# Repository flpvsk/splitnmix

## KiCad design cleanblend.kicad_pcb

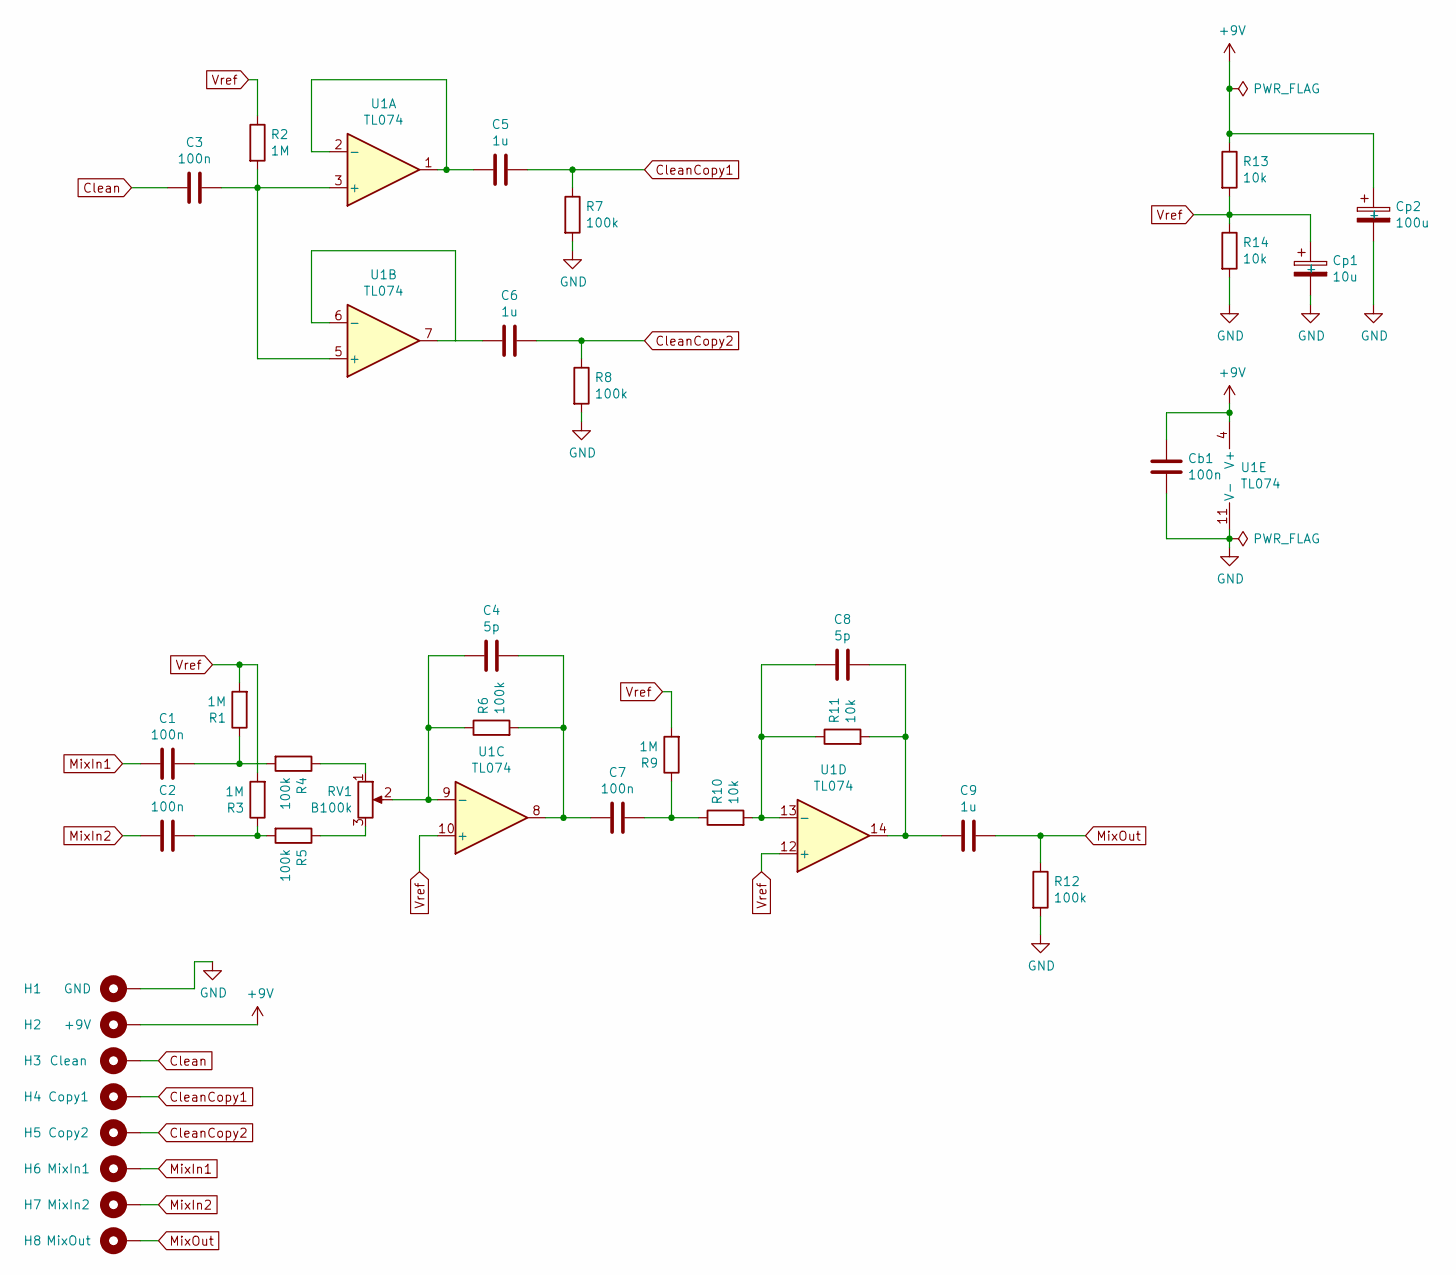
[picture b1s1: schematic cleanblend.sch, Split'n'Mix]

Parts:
C1, C2, C3, C7: 100n; C_0805_2012Metric_Pad1.15x1.40mm_HandSolder; JLC C49678
C4, C8: 5p; C_0603_1608Metric_Pad1.05x0.95mm_HandSolder; JLC C93045
C5, C6, C9: 1u; C_0805_2012Metric_Pad1.15x1.40mm_HandSolder; JLC C28323
Cb1: 100n; C_0805_2012Metric_Pad1.15x1.40mm_HandSolder; JLC C49678
Cp1: 10u; CP_Elec_5x5.3; JLC C249452
Cp2: 100u; CP_Elec_6.3x7.7; JLC C171732
H1: GND; PinHeader_1x01_P2.54mm_Long_Front_Back
H2: +9V; PinHeader_1x01_P2.54mm_Long_Front_Back
H3: Clean; PinHeader_1x01_P2.54mm_Long_Front_Back
H4: Copy1; PinHeader_1x01_P2.54mm_Long_Front_Back
H5: Copy2; PinHeader_1x01_P2.54mm_Long_Front_Back
H6: MixIn1; PinHeader_1x01_P2.54mm_Long_Front_Back
H7: MixIn2; PinHeader_1x01_P2.54mm_Long_Front_Back
H8: MixOut; PinHeader_1x01_P2.54mm_Long_Front_Back
R1, R2, R3, R9: 1M; R_0603_1608Metric_Pad1.05x0.95mm_HandSolder
R4, R5, R6, R7, R8, R12: 100k; R_0603_1608Metric_Pad1.05x0.95mm_HandSolder
R10, R11, R13, R14: 10k; R_0603_1608Metric_Pad1.05x0.95mm_HandSolder
RV1: B100k; 9MM_METAL_SHAFT
U1: TL074; SOIC-14_3.9x8.7mm_P1.27mm

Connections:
+9V: Cb1.1, Cp2.1 (+), H2.1, R13.1, U1.4 (V+); also elsewhere on the board
Clean: C3.2, H3.1
CleanCopy1: C5.1, H4.1, R7.1
CleanCopy2: C6.1, H5.1, R8.1
GND: Cb1.2, Cp1.2 (-), Cp2.2 (-), H1.1, R7.2, R8.2, R12.2, R14.2, U1.11 (V-); also elsewhere on the board
MixIn1: C1.2, H6.1
MixIn2: C2.2, H7.1
MixOut: C9.1, H8.1, R12.1
unnamed: C1.1, R1.1, R4.2
unnamed: C2.1, R3.1, R5.2
unnamed: C3.1, R2.2, U1.3 (+), U1.5 (+)
unnamed: C4.1, C7.2, R6.2, U1.8
unnamed: C4.2, R6.1, RV1.2, U1.9 (-)
unnamed: C5.2, U1.1, U1.2 (-)
unnamed: C6.2, U1.6 (-), U1.7
unnamed: C7.1, R9.1, R10.1
unnamed: C8.1, C9.2, R11.2, U1.14
unnamed: C8.2, R10.2, R11.1, U1.13 (-)
unnamed: R4.1, RV1.1
unnamed: R5.1, RV1.3
Vref: Cp1.1 (+), R1.2, R2.1, R3.2, R9.2, R13.2, R14.1, U1.10 (+), U1.12 (+)

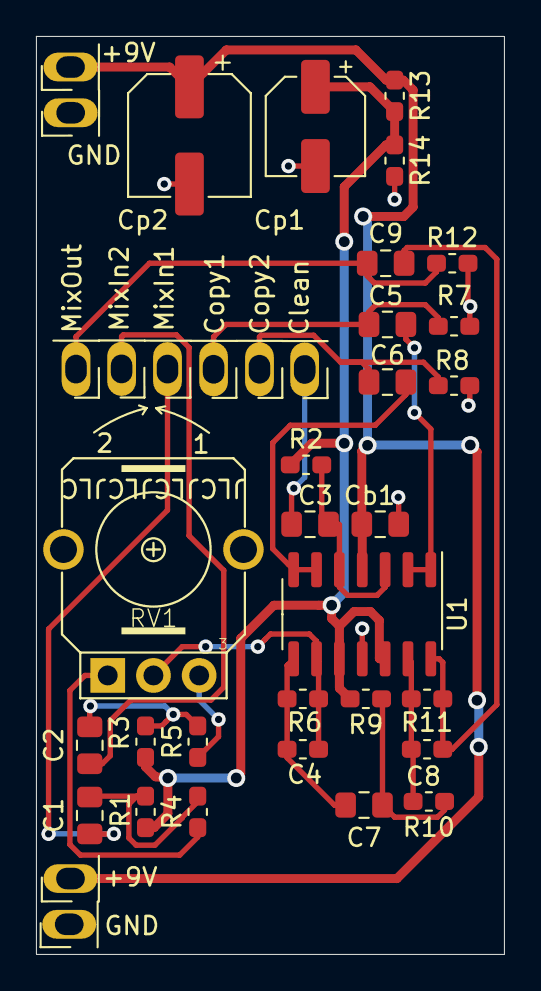
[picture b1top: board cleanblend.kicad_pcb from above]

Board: 2 copper layers, 26.0 x 51.0 mm, 38 parts (1 on the bottom side), 21 nets.

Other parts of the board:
H1#2: GND; PinHeader_1x01_P2.54mm_Long_Front_Back
H2#2: +9V; PinHeader_1x01_P2.54mm_Long_Front_Back

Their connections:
+9V: H2#2.1; also elsewhere on the board
GND: H1#2.1; also elsewhere on the board

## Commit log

2021-09-10 TMP breadboard design
2021-09-10 SplitNMix breadboard start
2021-09-13 Breadboard version
